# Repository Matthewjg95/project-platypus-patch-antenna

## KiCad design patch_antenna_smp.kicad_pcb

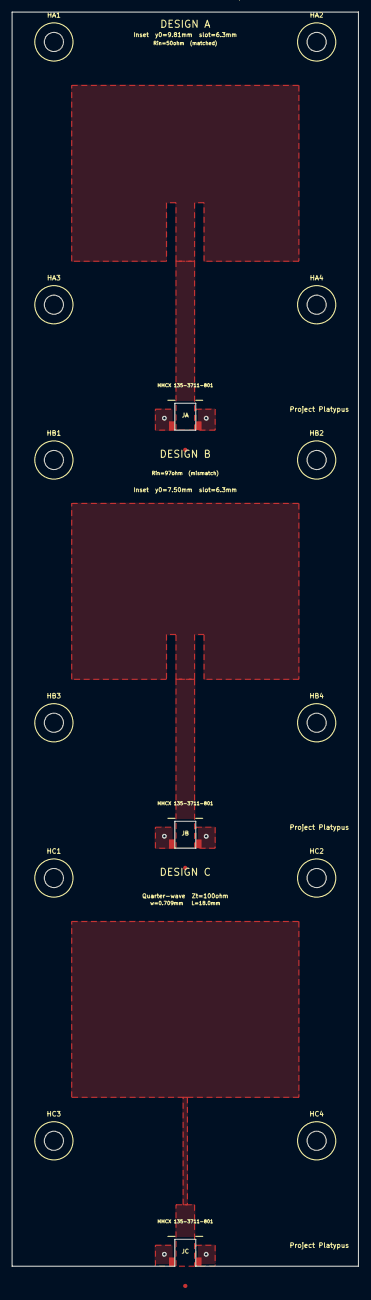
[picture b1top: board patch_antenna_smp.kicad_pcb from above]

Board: 2 copper layers, 58.0 x 210.0 mm, 15 parts (0 on the bottom side), 2 nets, no tracks yet.

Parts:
HA1, HA2, HA3, HA4: M3; M3_NPTPH
HB1, HB2, HB3, HB4: M3; M3_NPTPH
HC1, HC2, HC3, HC4: M3; M3_NPTPH
JA: MMCX-135-3711-801; MMCX_135-3711-801
JB: MMCX-135-3711-801; MMCX_135-3711-801
JC: MMCX-135-3711-801; MMCX_135-3711-801

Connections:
GND: JA.2, JA.3, JB.2, JB.3, JC.2, JC.3
RF_IN: JA.1, JB.1, JC.1
